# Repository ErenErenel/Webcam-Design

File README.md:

# Custom Embedded Webcam (SAM4S8B + OV2640 + ESP32)

A custom webcam system that captures JPEG images on a SAM4S8B microcontroller and
streams them to a browser over Wi-Fi via an ESP32 module. This repository contains
both the **PCB hardware design** and the **microcontroller firmware**.

Developed for **EE 326: Electronic System Design 1** at Northwestern University.

## System Overview

```
 OV2640 camera ──(parallel + I²C)──► SAM4S8B MCU ──(UART + SPI)──► ESP32 Wi-Fi ──► Browser
```

- The **OV2640** captures JPEG frames at 320×240, clocked into the MCU over an
  8-bit parallel interface using the SAM4S Peripheral DMA Controller (PDC).
  Camera registers are configured over I²C (TWI) at 400 kHz.
- The **SAM4S8B** (Cortex-M4) initializes the camera, detects JPEG frame length,
  and pushes image data to the ESP32 over SPI.
- The **ESP32-WROOM-32E** runs Wi-Fi provisioning, hosts a websocket server, and
  serves the streamed images to connected web clients. The MCU controls it through
  UART commands and monitors network/client status over GPIO.

## Repository Structure

```
Webcam-Design/
├── Hardware/      KiCad PCB design (schematic, layout, design rules)
│   ├── Ereno2.kicad_sch     Schematic
│   ├── Ereno2.kicad_pcb     Board layout
│   ├── Ereno2.kicad_pro     KiCad project
│   └── Ereno2.kicad_dru     Custom design rules
└── Firmware/      Atmel Studio (ASF) firmware for the SAM4S8B
    └── ErenFirmware/
        └── ErenFirmware/src/
            ├── main.c                  Boot, peripheral init, stream loop
            ├── camera.c / camera.h     OV2640 capture (PDC, JPEG framing)
            ├── ov2640.c / ov2640.h     OV2640 register driver + register tables
            ├── wifi.c / wifi.h         ESP32 UART command + SPI image transfer
            ├── timer_interface.c/.h    Timer/counter setup
            └── config/                 Board, clock, and UART configuration
```

## Firmware Flow

1. **Init** — system clock, watchdog disable, I/O ports, timer, USART, SPI, camera.
2. **ESP32 setup** — hard-reset the ESP32, then assign its GPIO roles
   (comm, network status, client status, provisioning, indicator LEDs) and SPI baud
   rate via UART commands.
3. **Connect** — wait for the ESP32 to join a network, handling provisioning requests
   from the on-board setup button; retry with `test`/reset until the link reports `SUCCESS`.
4. **Stream** — while a network and at least one client are connected, capture a frame
   and transfer it to the ESP32 for web display.

## Building the Firmware

The firmware targets the **ATSAM4S8B** and is built with **Microchip (Atmel) Studio 7**
using the Advanced Software Framework (ASF).

1. Open `Firmware/ErenFirmware/ErenFirmware.atsln` in Microchip Studio.
2. Build (`F7`) — output is generated in `Debug/` (ignored by git).
3. Flash to the board using a SAM-compatible programmer/debugger.

## Hardware

Open `Hardware/Ereno2.kicad_pro` in **KiCad 7+** to view or edit the schematic and
board layout. Key components: SAM4S8B MCU, OV2640 camera module, and an
ESP32-WROOM-32E-N4 Wi-Fi module.

## License

Released under the [MIT License](LICENSE).

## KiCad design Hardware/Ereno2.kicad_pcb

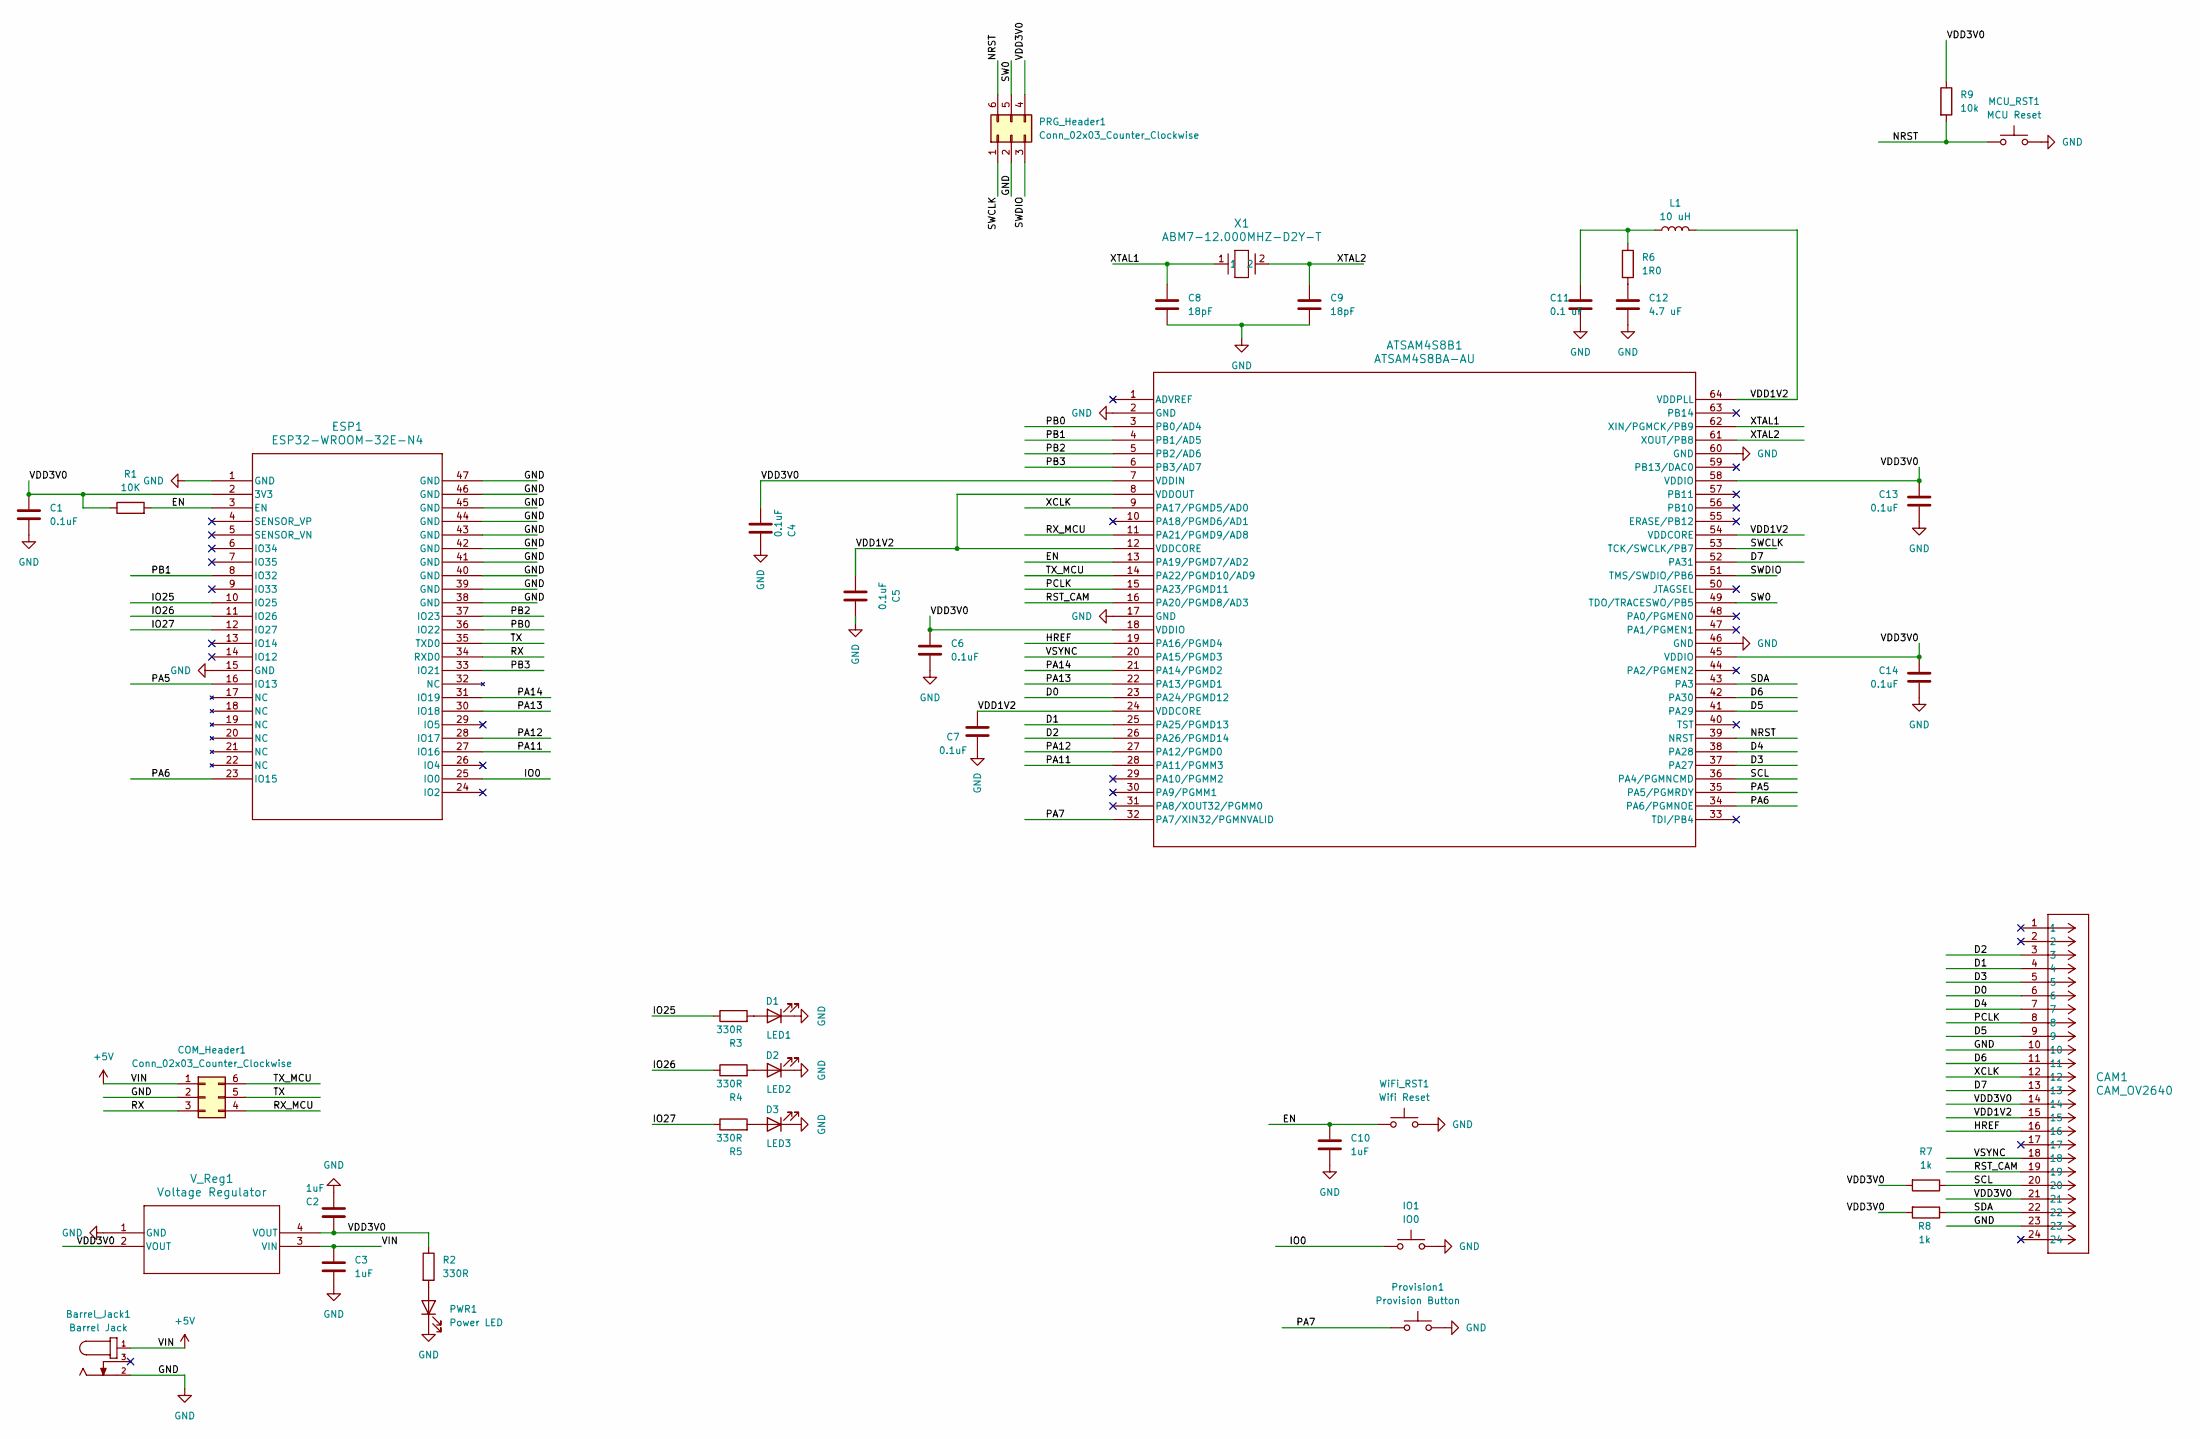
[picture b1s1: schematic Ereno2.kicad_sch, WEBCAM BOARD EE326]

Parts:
ATSAM4S8B1: ATSAM4S8BA-AU; LQFP64-2_ATM
Barrel_Jack1: Barrel Jack; 694106106102; DigiKey_Part_Number 732-5929-1-ND
C1, C4, C5, C6, C7, C13, C14: 0.1uF; C_0805_2012Metric
C2, C3, C10: 1uF; C_0805_2012Metric
C8, C9: 18pF; C_0805_2012Metric
C11: 0.1 uF; C_0805_2012Metric
C12: 4.7 uF; C_0805_2012Metric
CAM1: CAM_OV2640; CAM_CONN
COM_Header1: Conn_02x03_Counter_Clockwise; PinHeader_2x03_P2.54mm_Vertical
D1: LED1; LED_0201_0603Metric
D2: LED2; LED_0201_0603Metric
D3: LED3; LED_0201_0603Metric
ESP1: ESP32-WROOM-32E-N4; ESP32­WROOM­32E_EXP
IO1: IO0; pushbutton (1)
L1: 10 uH; L_0805_2012Metric
MCU_RST1: MCU Reset; pushbutton (1)
PRG_Header1: Conn_02x03_Counter_Clockwise; PinHeader_2x03_P2.54mm_Vertical
PWR1: Power LED; LED_0201_0603Metric_Pad0.64x0.40mm_HandSolder
Provision1: Provision Button; pushbutton (1)
R1: 10K; R_0805_2012Metric
R2, R3, R4, R5: 330R; R_0805_2012Metric
R6: 1R0; R_0805_2012Metric
R7, R8: 1k; R_0805_2012Metric
R9: 10k; R_0805_2012Metric
V_Reg1: Voltage Regulator; SOT223_STM
WiFi_RST1: Wifi Reset; pushbutton (1)
X1: ABM7-12.000MHZ-D2Y-T; XTAL_ABM7_ABR

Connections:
/D0: ATSAM4S8B1.23 (PA24/PGMD12), CAM1.6
/D1: ATSAM4S8B1.25 (PA25/PGMD13), CAM1.4
/D2: ATSAM4S8B1.26 (PA26/PGMD14), CAM1.3
/D3: ATSAM4S8B1.37 (PA27), CAM1.5
/D4: ATSAM4S8B1.38 (PA28), CAM1.7
/D5: ATSAM4S8B1.41 (PA29), CAM1.9
/D6: ATSAM4S8B1.42 (PA30), CAM1.11
/D7: ATSAM4S8B1.52 (PA31), CAM1.13
/EN: ATSAM4S8B1.13 (PA19/PGMD7/AD2), C10.1, ESP1.3 (EN), R1.2, WiFi_RST1.1
/HREF: ATSAM4S8B1.19 (PA16/PGMD4), CAM1.16
/IO0: ESP1.25 (IO0), IO1.1; also elsewhere on the board
/IO25: ESP1.10 (IO25), R3.1
/IO26: ESP1.11 (IO26), R4.1
/IO27: ESP1.12 (IO27), R5.1
/NRST: ATSAM4S8B1.39 (NRST), MCU_RST1.1, PRG_Header1.6, R9.2
/PA5: ATSAM4S8B1.35 (PA5/PGMRDY), ESP1.16 (IO13)
/PA6: ATSAM4S8B1.34 (PA6/PGMNOE), ESP1.23 (IO15)
/PA7: ATSAM4S8B1.32 (PA7/XIN32/PGMNVALID), Provision1.1
/PA11: ATSAM4S8B1.28 (PA11/PGMM3), ESP1.27 (IO16)
/PA12: ATSAM4S8B1.27 (PA12/PGMD0), ESP1.28 (IO17)
/PA13: ATSAM4S8B1.22 (PA13/PGMD1), ESP1.30 (IO18)
/PA14: ATSAM4S8B1.21 (PA14/PGMD2), ESP1.31 (IO19)
/PB0: ATSAM4S8B1.3 (PB0/AD4), ESP1.36 (IO22)
/PB1: ATSAM4S8B1.4 (PB1/AD5), ESP1.8 (IO32)
/PB2: ATSAM4S8B1.5 (PB2/AD6), ESP1.37 (IO23)
/PB3: ATSAM4S8B1.6 (PB3/AD7), ESP1.33 (IO21)
/PCLK: ATSAM4S8B1.15 (PA23/PGMD11), CAM1.8
/RST_CAM: ATSAM4S8B1.16 (PA20/PGMD8/AD3), CAM1.19
/RX: COM_Header1.3, ESP1.34 (RXD0)
/RX_MCU: ATSAM4S8B1.11 (PA21/PGMD9/AD8), COM_Header1.4
/SCL: ATSAM4S8B1.36 (PA4/PGMNCMD), CAM1.20, R7.1
/SDA: ATSAM4S8B1.43 (PA3), CAM1.22, R8.1
/SW0: ATSAM4S8B1.49 (TDO/TRACESWO/PB5), PRG_Header1.5
/SWCLK: ATSAM4S8B1.53 (TCK/SWCLK/PB7), PRG_Header1.1
/SWDIO: ATSAM4S8B1.51 (TMS/SWDIO/PB6), PRG_Header1.3
/TX: COM_Header1.5, ESP1.35 (TXD0)
/TX_MCU: ATSAM4S8B1.14 (PA22/PGMD10/AD9), COM_Header1.6
/VDD1V2: ATSAM4S8B1.8 (VDDOUT), ATSAM4S8B1.12 (VDDCORE), ATSAM4S8B1.24 (VDDCORE), ATSAM4S8B1.54 (VDDCORE), ATSAM4S8B1.64 (VDDPLL), C5.1, C7.1, CAM1.15, L1.2
/VDD3V0: ATSAM4S8B1.7 (VDDIN), ATSAM4S8B1.18 (VDDIO), ATSAM4S8B1.45 (VDDIO), ATSAM4S8B1.58 (VDDIO), C1.1, C2.1, C4.1, C6.1, C13.1, C14.1, CAM1.14, CAM1.21, ESP1.2 (3V3), PRG_Header1.4, R1.1, R2.1, R7.2, R8.2, R9.1, V_Reg1.2 (VOUT), V_Reg1.4 (VOUT)
/VIN: Barrel_Jack1.1, Barrel_Jack1.A1, C3.1, COM_Header1.1, V_Reg1.3 (VIN)
/VSYNC: ATSAM4S8B1.20 (PA15/PGMD3), CAM1.18
/XCLK: ATSAM4S8B1.9 (PA17/PGMD5/AD0), CAM1.12
/XTAL1: ATSAM4S8B1.62 (XIN/PGMCK/PB9), C8.1, X1.1
/XTAL2: ATSAM4S8B1.61 (XOUT/PB8), C9.1, X1.2
GND: ATSAM4S8B1.2 (GND), ATSAM4S8B1.17 (GND), ATSAM4S8B1.46 (GND), ATSAM4S8B1.60 (GND), Barrel_Jack1.2, C1.2, C2.2, C3.2, C4.2, C5.2, C6.2, C7.2, C8.2, C9.2, C10.2, C11.2, C12.2, C13.2, C14.2, CAM1.10, CAM1.23, COM_Header1.2, D1.1 (K), D2.1 (K), D3.1 (K), ESP1.1 (GND), ESP1.15 (GND), ESP1.38 (GND), ESP1.39 (GND), ESP1.40 (GND), ESP1.41 (GND), ESP1.42 (GND), ESP1.43 (GND), ESP1.44 (GND), ESP1.45 (GND), ESP1.46 (GND), ESP1.47 (GND), IO1.2, MCU_RST1.2, PRG_Header1.2, PWR1.1 (K), Provision1.2, V_Reg1.1 (GND), WiFi_RST1.2; also elsewhere on the board
unnamed: C11.1, L1.1, R6.1
unnamed: C12.1, R6.2
unnamed: D1.2 (A), R3.2
unnamed: D2.2 (A), R4.2
unnamed: D3.2 (A), R5.2
unnamed: PWR1.2 (A), R2.2

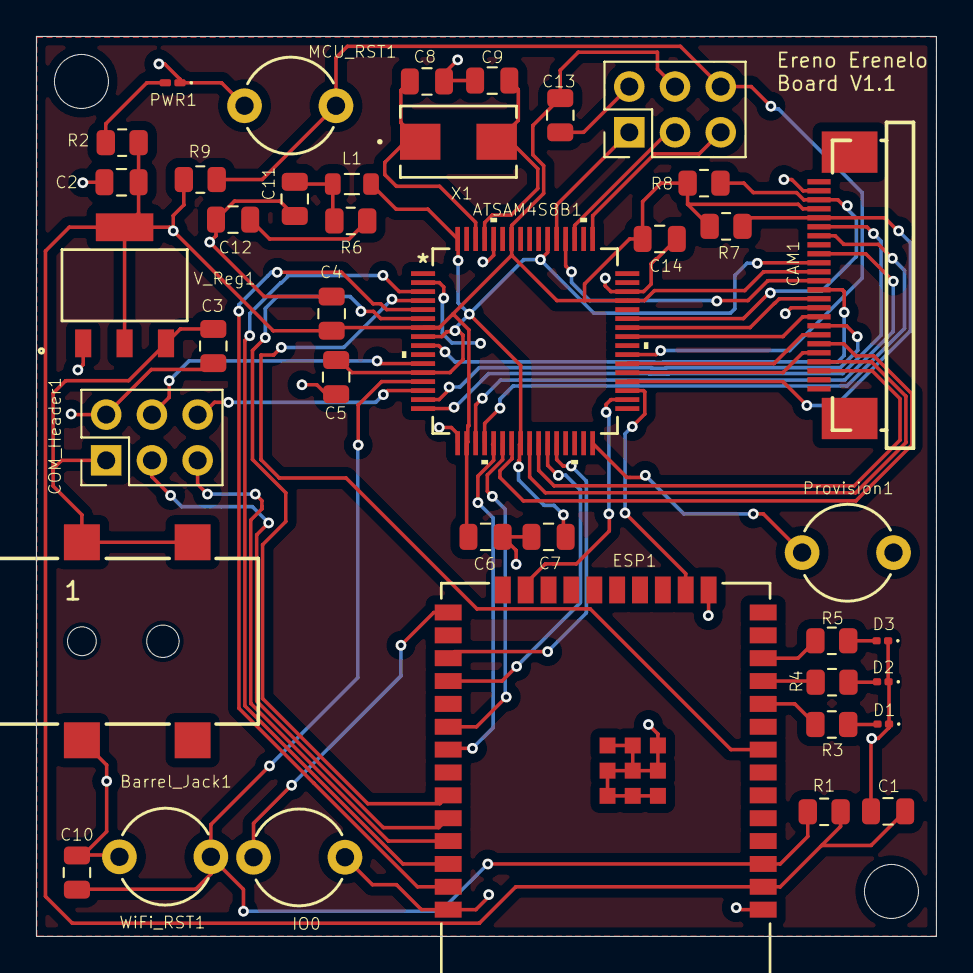
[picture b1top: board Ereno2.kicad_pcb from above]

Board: 2 copper layers, 50.0 x 50.0 mm, 40 parts (0 on the bottom side), 51 nets.

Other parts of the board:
IO0: IO0; pushbutton (1)

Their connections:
/IO0: IO0.1; also elsewhere on the board
GND: IO0.2; also elsewhere on the board

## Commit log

2026-03-03 pcb files
2026-06-25 Add .gitignore and commit updated KiCad schematic and project files
2026-06-25 Restructure into Hardware/ and Firmware/; merge in SAM4S webcam firmware
    - Rename "Webcam PCB" -> Hardware/ for a clear modular layout
    - Add Firmware/ containing the SAM4S8B firmware (camera, OV2640, Wi-Fi)
    previously in the standalone EE326_Firmware repo
    - Untrack KiCad autosave file; ignore firmware build artifacts
2026-06-25 Write detailed README covering system, structure, firmware flow, and build
